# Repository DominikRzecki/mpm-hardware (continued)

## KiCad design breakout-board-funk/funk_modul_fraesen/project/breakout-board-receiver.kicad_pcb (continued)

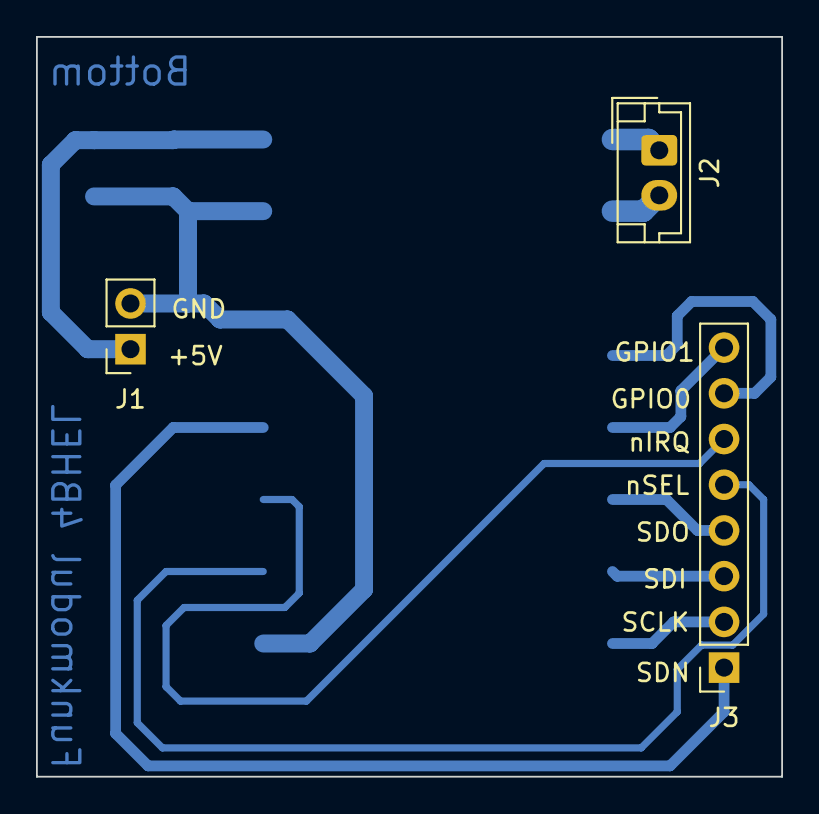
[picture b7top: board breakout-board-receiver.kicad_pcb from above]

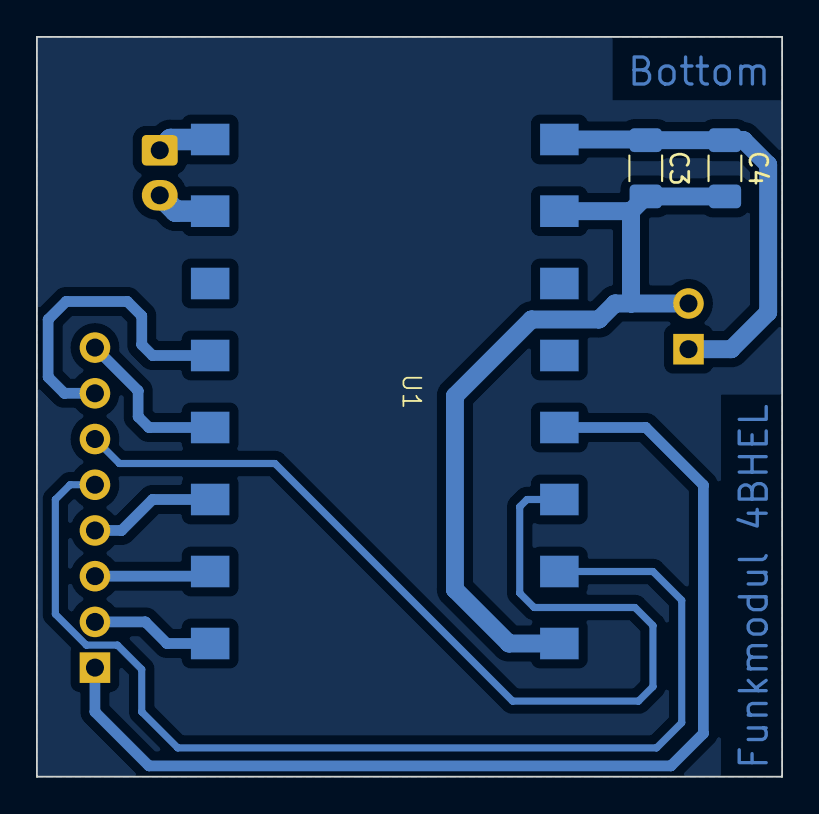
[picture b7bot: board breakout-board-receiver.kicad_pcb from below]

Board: 2 copper layers, 41.4 x 41.1 mm, 6 parts (3 on the bottom side), 12 nets.

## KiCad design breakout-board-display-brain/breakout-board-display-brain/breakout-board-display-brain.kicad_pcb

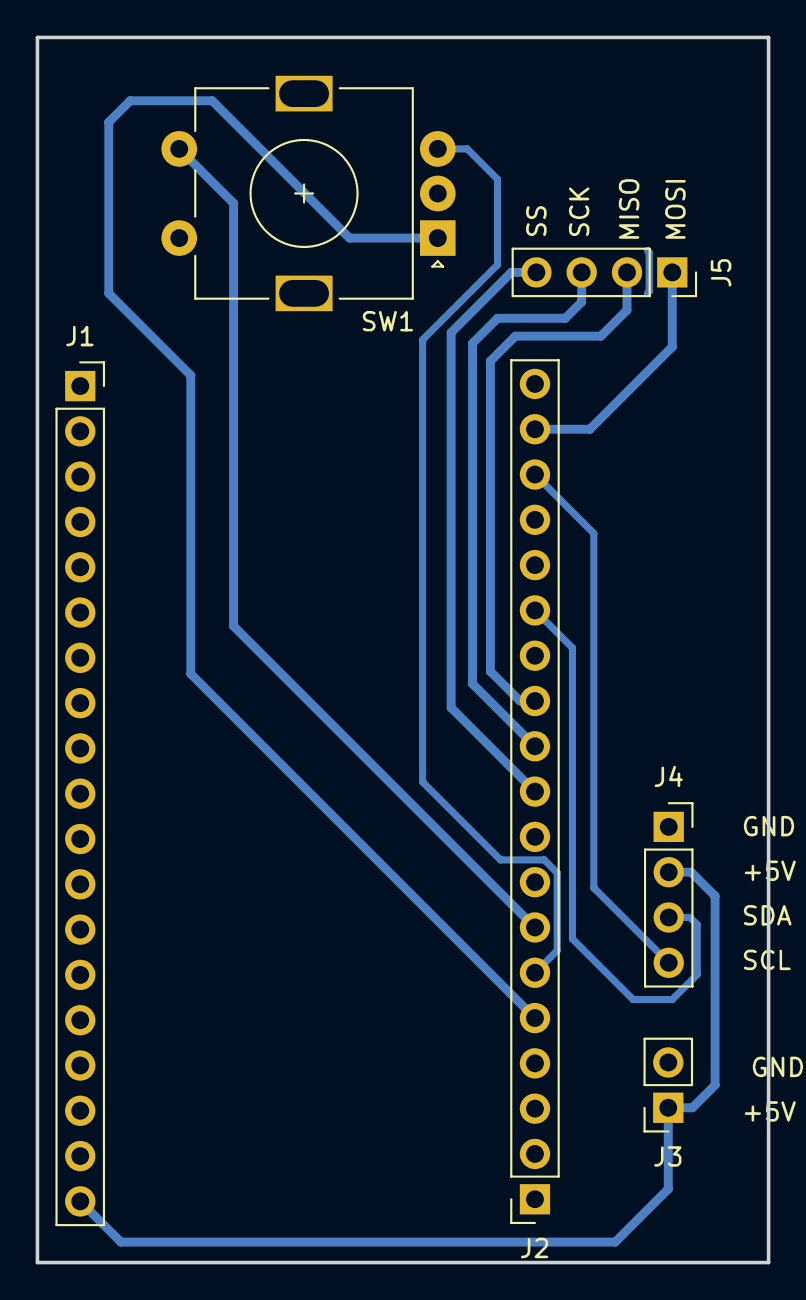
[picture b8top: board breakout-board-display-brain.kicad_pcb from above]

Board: 2 copper layers, 41.0 x 68.7 mm, 6 parts (0 on the bottom side), 11 nets.

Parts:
J1, J2: Conn_01x19_Socket; PinSocket_1x19_P2.54mm_Vertical
J3: Conn_01x02_Socket; PinSocket_1x02_P2.54mm_Vertical
J4, J5: Conn_01x04_Socket; PinSocket_1x04_P2.54mm_Vertical
SW1: RotaryEncoder_Switch; RotaryEncoder_Alps_EC11E-Switch_Vertical_H20mm

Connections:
+5V: J1.19, J3.1, J4.2
/IO0: J2.6, SW1.B
/IO2: J2.5, SW1.A
/IO4: J2.7, SW1.S1
/IO5_SS: J2.10, J5.4
/IO18_SCK: J2.11, J5.3
/IO19_MISO: J2.12, J5.2
/IO21_SDA: J2.14, J4.3
/IO22_SCL: J2.17, J4.4
/IO23_MOSI: J2.18, J5.1
GND: J1.14, J2.13, J2.19, J3.2, J4.1, SW1.C, SW1.S2

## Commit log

2023-02-01 Ich habe das und das verändert
2023-02-01 der Schaltplan für das module-brain-display Modul wurde zum GitHub Reposetory hinzugefügt
2023-02-01 Kicad Projektdateien für Epmfänger und Sender wurden von Laci hinzugefügt
2023-02-01 der Schaltplan des attiny breakout boards wurde verschönert
2023-02-01 Added breakout for power measurement module on the high voltage side.
2023-02-01 kicad datei für das powersupply breakout board wurde erstellt
2023-02-03 Das atTiny breajout board ist fertig!
    Laci hat einige Dinge an den breakout boards geändert
2023-02-04 Schaltpläne und PCB-Layouts wurden erstellt
    allerdings noch nicht fertig gemacht
2023-02-12 Started work for the power measurement breakout board. Added shunt resitor and a voltage divider + few caps
2023-02-14 test
    test
2023-02-14 Revert "..."
    This reverts commit 6093de15b6a411821706cd1d809fe7ad2ca1dc62.
2023-02-14 KiCad 7.0
    Updated to KiCad 7.0 file format
2023-02-15 test
2023-02-17 ATtiny breakout board done
2023-02-17 ATtiny breakout board finished and ready for production
2023-02-17 display brain breakout board changed
2023-02-17 Added power measurement README.md (docs)
2023-02-21 Amir approved: Rotary Encode Circuit
2023-02-21 Update: nun approved!
2023-02-21 further work on breakout board display brain
2023-02-21 brbrain
2023-02-21 connector added to display-brain breakout board
2023-02-21 Routing
2023-02-21 updated power measurement circuit
2023-02-23 minor changes
2023-02-24 Major improvements: Power measurement schematic almost done.
2023-02-25 Added breakout board for simple X-Cap power supply.
2023-02-28 plots generated for attiny breakout board
2023-02-28 Safety circuit and x-cap psu circuit added.
2023-02-28 changes made to attiny and display brain breakout board
2023-03-03 receiver and transmitter breakout board changed
2023-03-04 LTSpice .raw files wont be uploaded any more. power-measurement breakout will be finished tomorrow
2023-03-04 power measurement schematic organized
2023-03-04 display-brain modified
2023-03-05 finsihed breakout-board.display-brain
    fertig fürs Fräsen
2023-03-05 some footprints added
2023-03-06 Major updates: Power Measurement PCB-routing half way done.
2023-03-06 Added MCP3911 lib to project specific libraries
2023-03-07 Important updates and fine tunings to schematic
2023-03-09 Power measurement PCB 95% Done. Whats missing: proper cooil footprints, capacitive power supply net
2023-03-10 funk breakout board routed
2023-03-10 funk breakout board finished and sent out for manufacturing
2023-03-12 Breakout Board: Power Measurement - status: done.. yaygit add -A!
2023-03-14 Revert "Merge branch 'main' of https://github.com/DominikRzecki/mpm-hardware"
    This reverts commit b1fb40005cc6000a652d43f250fbd6541baa0df3, reversing
    changes made to 77b873b98367f4cea487d2747d29dc0cf0db4d54.
2023-03-14 pcb backup restored
2023-03-14 Restored old order
2023-03-14 plot files generated for manufacturing
2023-03-14 Changed vias to test points
2023-03-14 entgültige boards zum fräsen geschickt
2023-03-14 Added component list
2023-03-19 Fixed Power Measurement PCB, important changes.
2023-03-19 Minor Fixes.
2023-03-19 Power measurement PCB plotted. Laci please check if the plot is correct.
2023-03-19 power measurement fertig fürs fräsen
2023-03-28 neue ordner erstellt
2023-03-31 display final finished
2023-03-31 funk-final finished
2023-03-31 funk finished
2023-03-31 display brain platine fertig
2023-03-31 display brain platine erweitert
2023-03-31 funk platine fertig gemacht
2023-03-31 ATtiny platine fertig gestellt
2023-04-01 Increased width of power tracks from 0.2mm to 0.3mm
2023-04-01 5v versorgung für display geändert
2023-04-01 Replaced ASM1117 with LM317 in schematic.
2023-04-01 Updated PCB layout according to new schematic.(ASM1117-> LM317) (Beidl update)
2023-04-11 display and funk changed
2023-04-14 Fixed SPI
2023-04-14 Important fixes SDI/SDO swap, reset
2023-04-14 platinen angepasst
2023-04-14 punkt bei pin 1 der ics hinzugefügt
2023-04-25 power measuremnt final started
2023-04-28 power measurement final platine started
2023-04-28 power measuremnt final weitergemacht
2023-05-02 3D Druck V2/3
2023-05-02 finales power measurement modul weitergemacht
2023-05-05 rgergerg
2023-05-06 power measurement final almost completed
2023-05-06 small fixes
2023-05-08 Power measurement final almst ready
2023-05-08 various fixes
2023-05-08 Small changes
2023-05-09 SMPS routed
2023-05-09 power rmeasurement final finished
2023-05-12 funk plot
2023-05-12 Updated power measurement
